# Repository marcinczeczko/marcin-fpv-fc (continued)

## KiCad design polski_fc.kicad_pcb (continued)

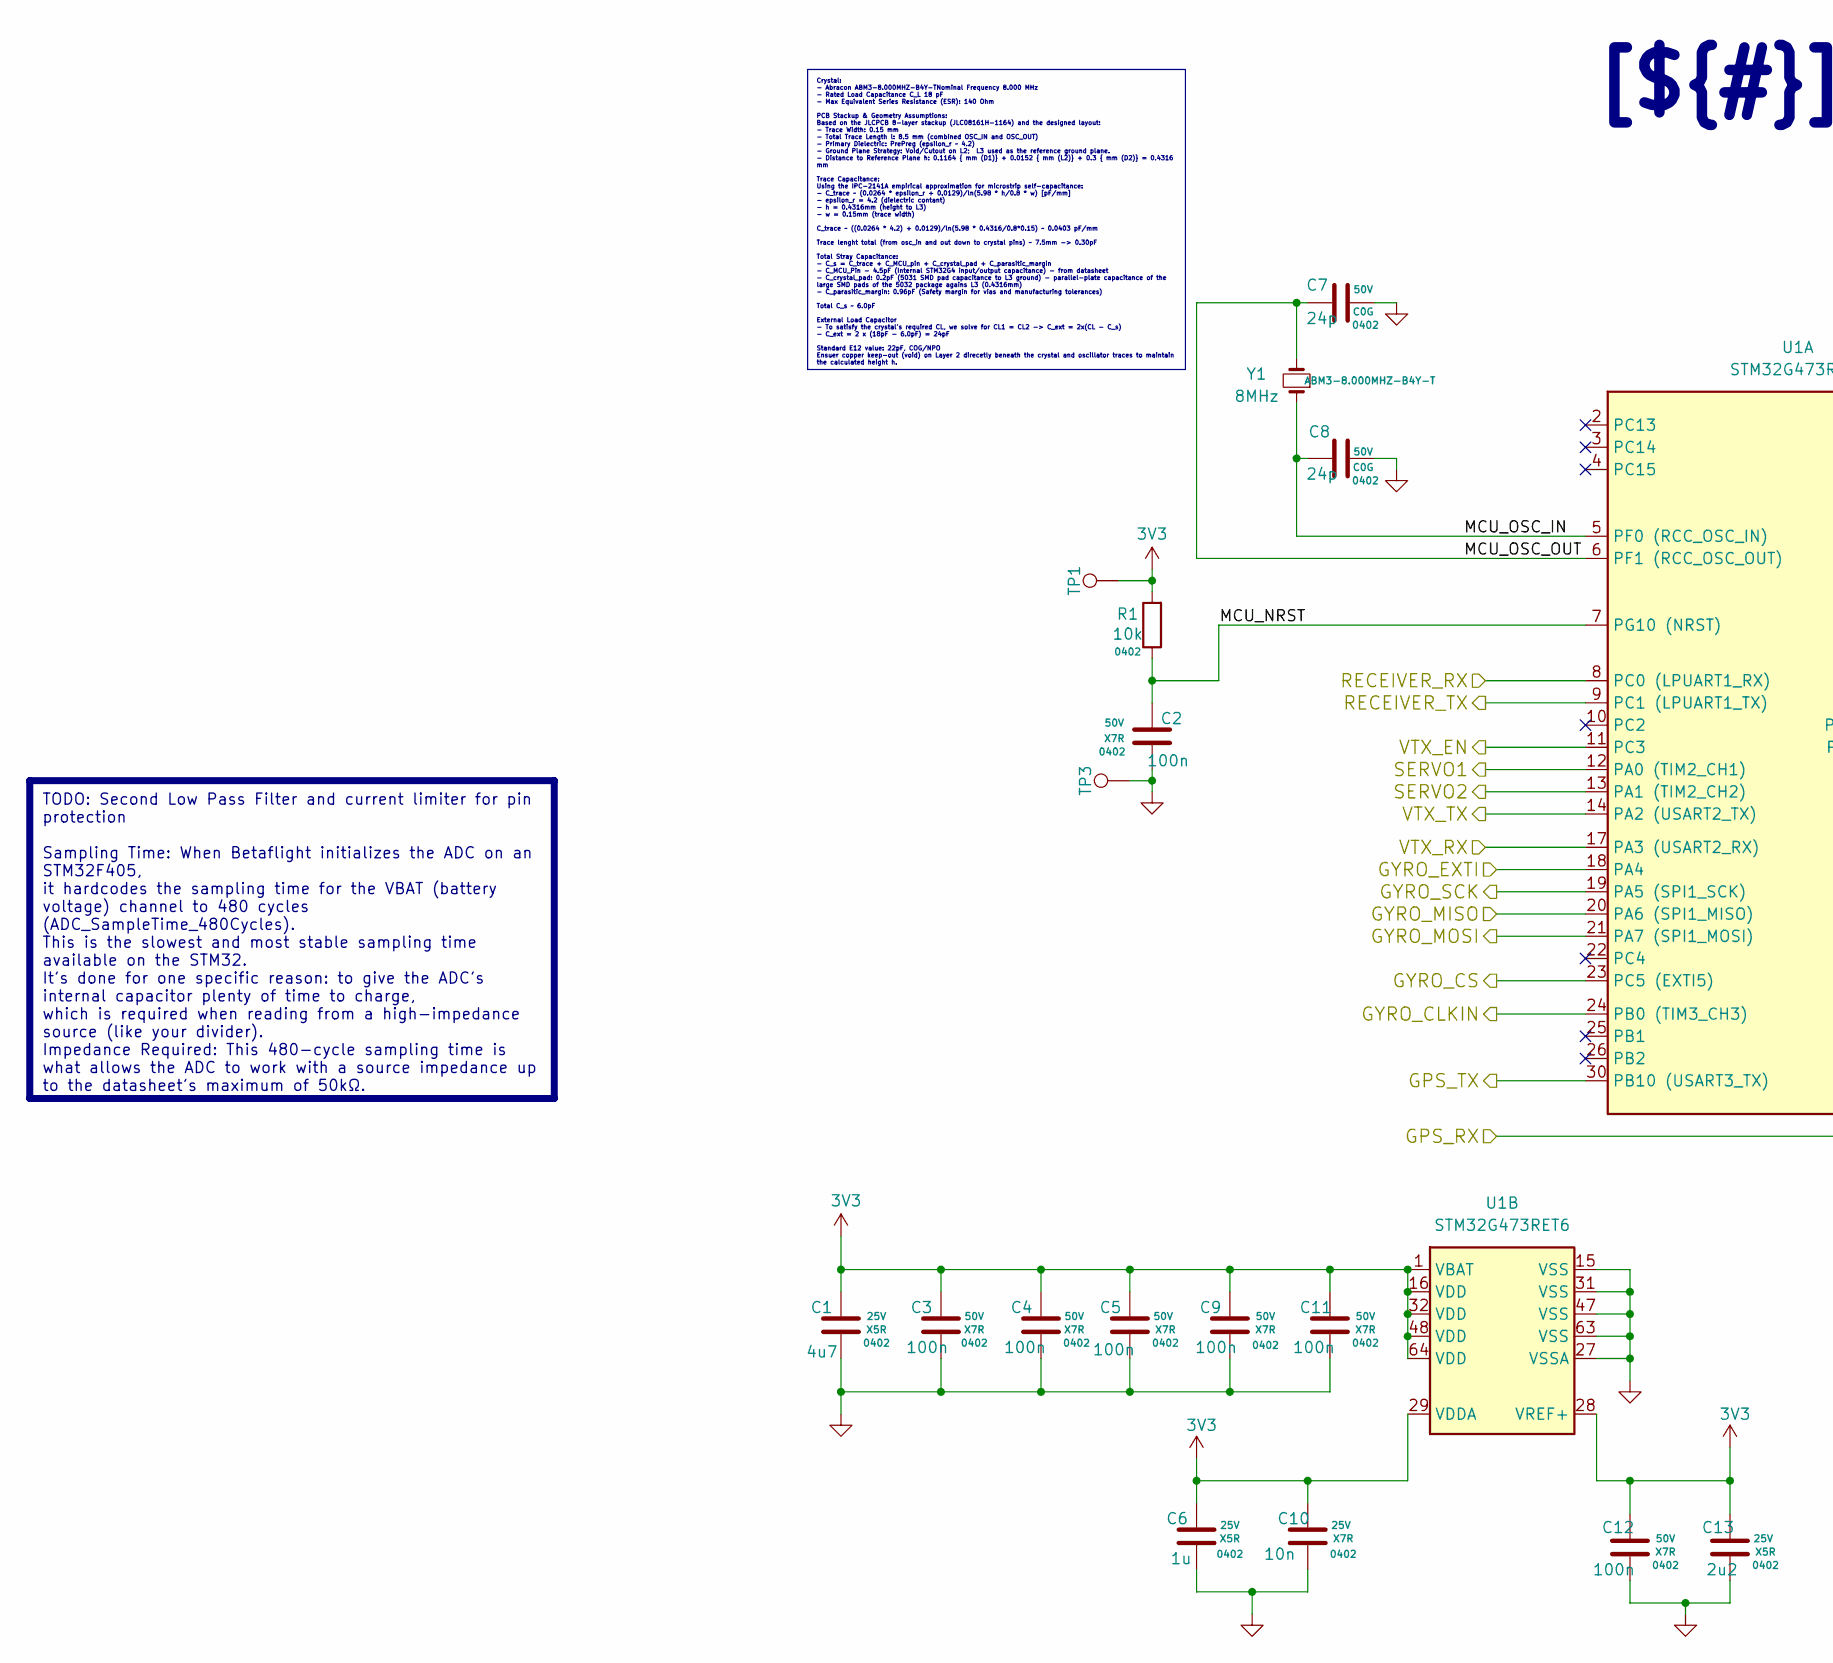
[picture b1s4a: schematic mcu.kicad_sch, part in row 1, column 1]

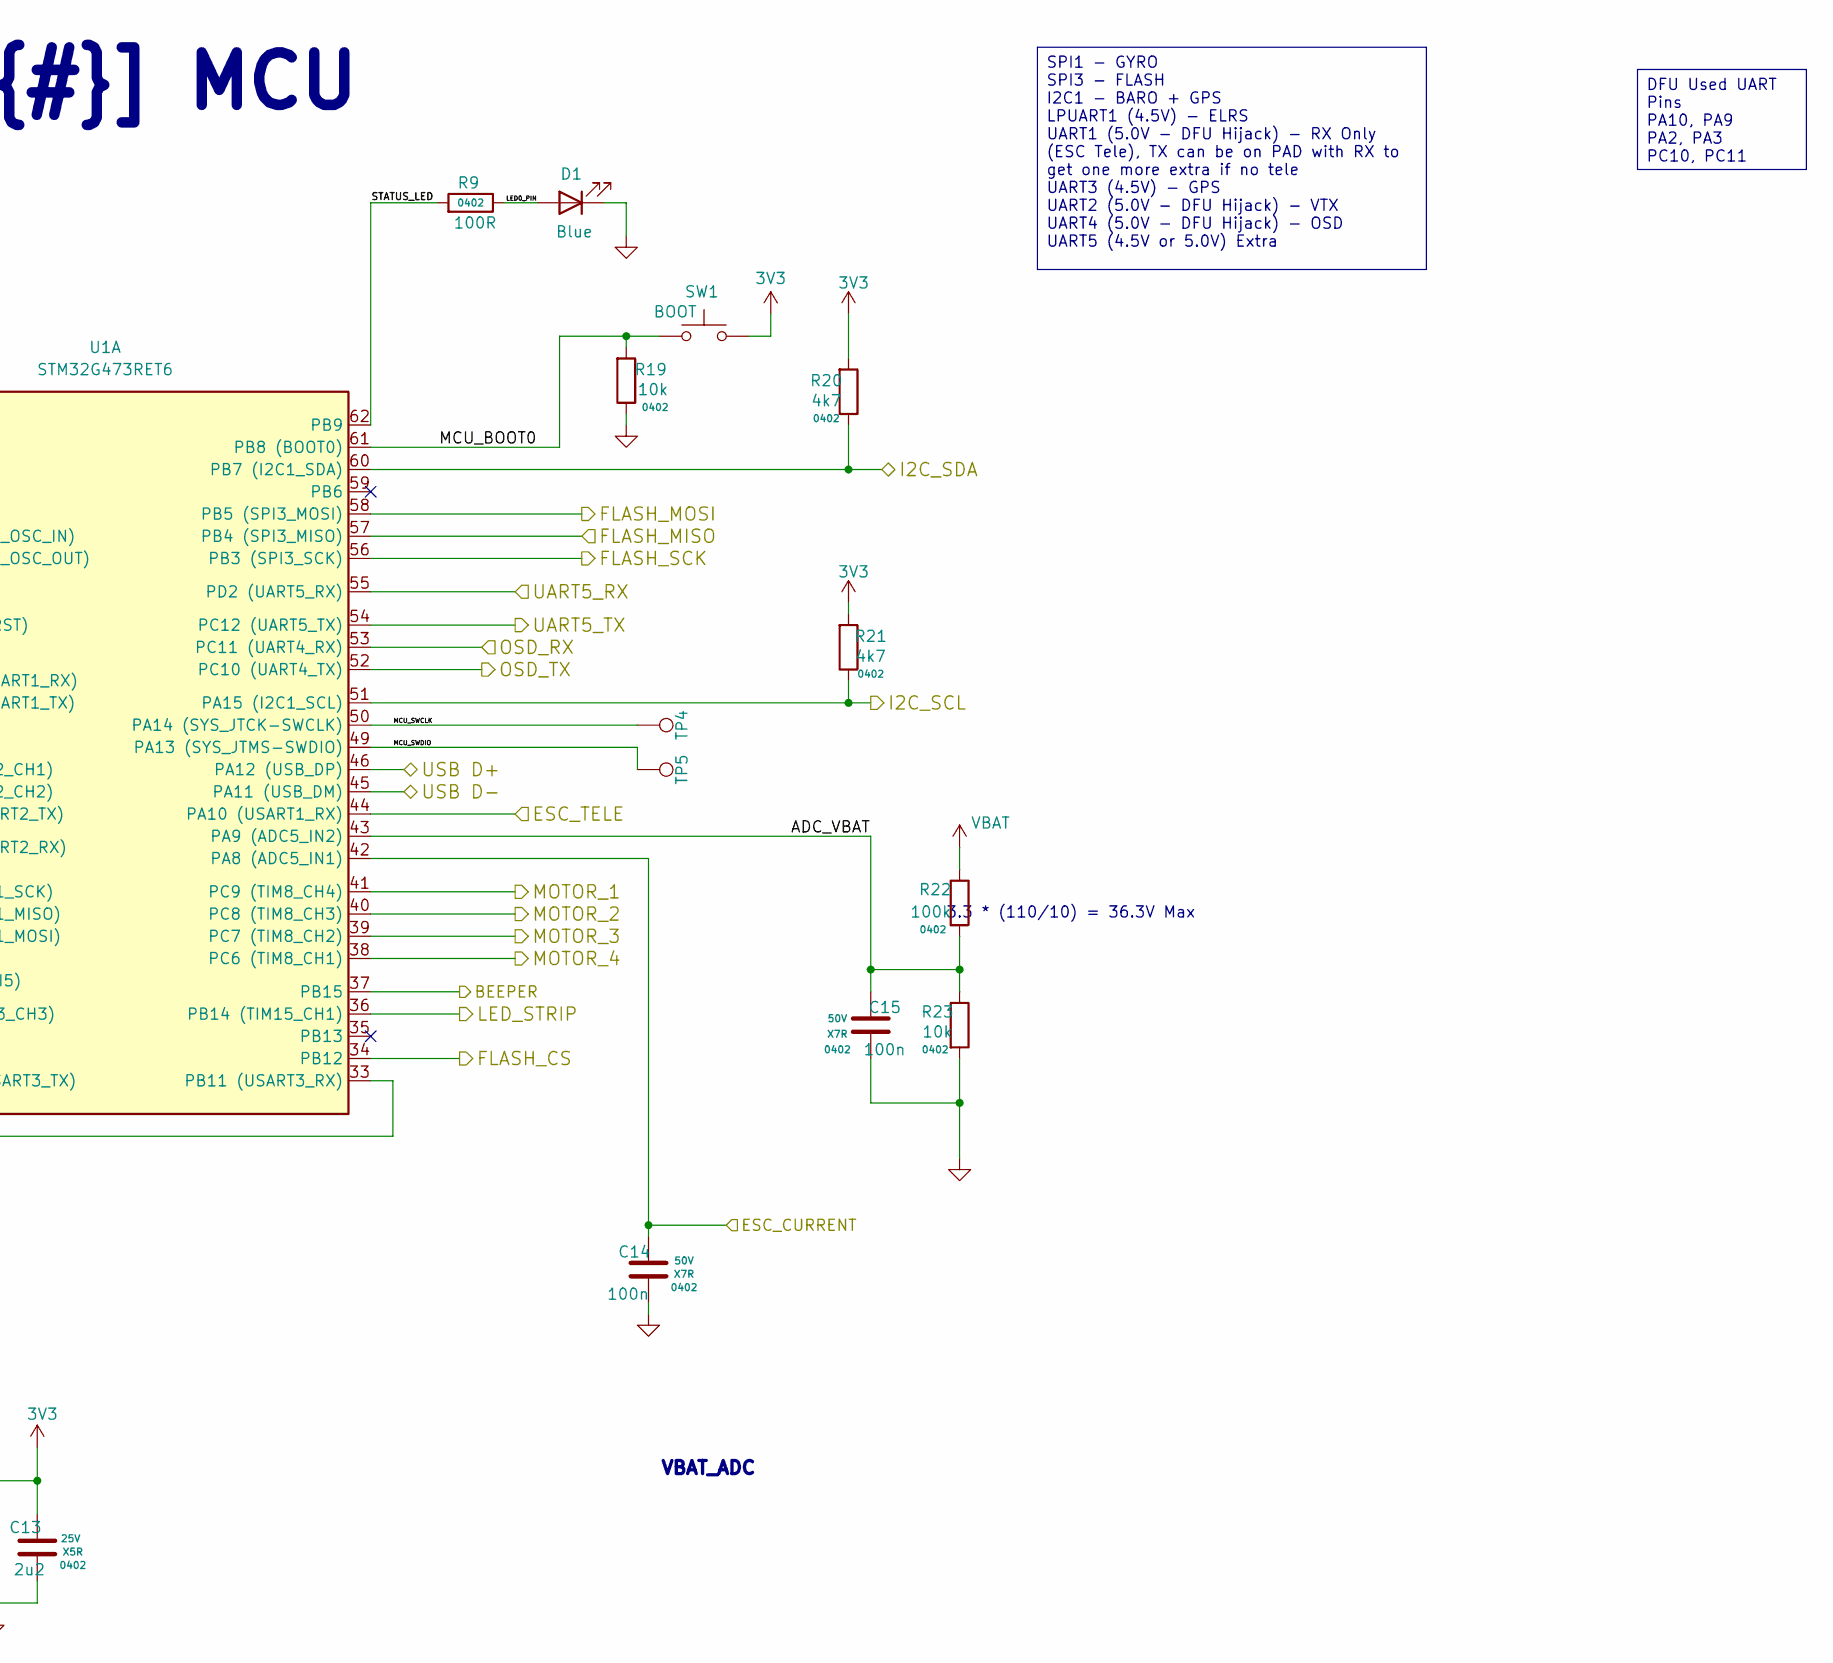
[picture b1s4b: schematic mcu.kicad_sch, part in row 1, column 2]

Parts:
C1: 4u7; C_0402; Voltage 25V; MANUFACTURER # GRM155R61C475KE15D; LCSC C426094
C2, C3, C4, C5, C9, C11, C12, C14, C15: 100n; C_0402; Voltage 50V; MANUFACTURER # GRM155R71H104KE14D; LCSC C77020
C6: 1u; C_0402; Voltage 25V; MANUFACTURER # GRM155R61E105KA12D; LCSC C77009
C7, C8: 24p; C_0402; Voltage 50V; MANUFACTURER # GCM1555C1H240FA16D; LCSC C1864480
C10: 10n; C_0402; Voltage 25V; MANUFACTURER # GRM155R71E103KA01D; LCSC C77013
C13: 2u2; C_0402; Voltage 25V; MANUFACTURER # GRM155R61E225KE11D; LCSC C385032
D1: Blue; LED_0402; MANUFACTURER # LTST-C281TBKT-5A; LCSC C364550
R1, R19, R23: 10k; R_0402; MANUFACTURER # RC0402FR-0710KL; LCSC C60490
R9: 100R; R_0402; MANUFACTURER # RC0402FR-07100RL; LCSC C106232
R20, R21: 4k7; R_0402; MANUFACTURER # RC0402JR-074K7L; LCSC C105870
R22: 100k; R_0402; MANUFACTURER # RP0402BRD07100KL; LCSC C7294193
SW1: BOOT; B3U-1000P; MANUFACTURER # B3U-1000P; LCSC C231329
TP1, TP3, TP4, TP5: 0.5mm; TestPoint-1mm
U1: STM32G473RET6; STM32G473RETx-LQFP-64_10x10mm_P0.5mm; MANUFACTURER # STM32G473RET6; LCSC C730120
Y1: 8MHz; ABM3; MANUFACTURER # ABM3-8.000MHZ-B4Y-T; Mouser # 815-ABM38000B4YT

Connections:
3V3: C1.1, C3.1, C4.1, C5.1, C6.1, C9.1, C10.1, C11.1, C12.1, C13.1, R1.1, R20.1, R21.1, SW1.1, TP1.1, U1.1 (VBAT), U1.16 (VDD), U1.28 (VREF+), U1.29 (VDDA), U1.32 (VDD), U1.48 (VDD), U1.64 (VDD); also elsewhere on the board
/Project Architecture/Blackbox/FLASH_CS: U1.34 (PB12); also elsewhere on the board
/Project Architecture/Blackbox/FLASH_DI: U1.58 (PB5 (SPI3_MOSI)); also elsewhere on the board
/Project Architecture/Blackbox/FLASH_DO: U1.57 (PB4 (SPI3_MISO)); also elsewhere on the board
/Project Architecture/Blackbox/FLASH_SCK: U1.56 (PB3 (SPI3_SCK)); also elsewhere on the board
/Project Architecture/IMU & Baro/BARO_I2C_SCL: R21.2, U1.51 (PA15 (I2C1_SCL)); also elsewhere on the board
/Project Architecture/IMU & Baro/BARO_I2C_SDA: R20.2, U1.60 (PB7 (I2C1_SDA)); also elsewhere on the board
/Project Architecture/IMU & Baro/GYRO_CLKIN: U1.24 (PB0 (TIM3_CH3)); also elsewhere on the board
/Project Architecture/IMU & Baro/GYRO_CS: U1.23 (PC5 (EXTI5)); also elsewhere on the board
/Project Architecture/IMU & Baro/GYRO_EXTI: U1.18 (PA4); also elsewhere on the board
/Project Architecture/IMU & Baro/GYRO_SCLK: U1.19 (PA5 (SPI1_SCK)); also elsewhere on the board
/Project Architecture/IMU & Baro/GYRO_SDI: U1.21 (PA7 (SPI1_MOSI)); also elsewhere on the board
/Project Architecture/IMU & Baro/GYRO_SDO: U1.20 (PA6 (SPI1_MISO)); also elsewhere on the board
/Project Architecture/Interfaces/BEEPER: U1.37 (PB15); also elsewhere on the board
/Project Architecture/Interfaces/ESC_CURR: C14.1, U1.42 (PA8 (ADC5_IN1)); also elsewhere on the board
/Project Architecture/Interfaces/LED_STRIP: U1.36 (PB14 (TIM15_CH1)); also elsewhere on the board
/Project Architecture/Interfaces/MOTOR1: U1.41 (PC9 (TIM8_CH4)); also elsewhere on the board
/Project Architecture/Interfaces/MOTOR2: U1.40 (PC8 (TIM8_CH3)); also elsewhere on the board
/Project Architecture/Interfaces/MOTOR3: U1.39 (PC7 (TIM8_CH2)); also elsewhere on the board
/Project Architecture/Interfaces/MOTOR4: U1.38 (PC6 (TIM8_CH1)); also elsewhere on the board
/Project Architecture/Interfaces/SERVO1: U1.12 (PA0 (TIM2_CH1)); also elsewhere on the board
/Project Architecture/Interfaces/SERVO2: U1.13 (PA1 (TIM2_CH2)); also elsewhere on the board
/Project Architecture/Interfaces/UART1_RX (RECV): U1.8 (PC0 (LPUART1_RX)); also elsewhere on the board
/Project Architecture/Interfaces/UART1_TX (RECV): U1.9 (PC1 (LPUART1_TX)); also elsewhere on the board
/Project Architecture/Interfaces/UART2_RX (TELE): U1.44 (PA10 (USART1_RX)); also elsewhere on the board
/Project Architecture/Interfaces/UART3_RX (GPS): U1.33 (PB11 (USART3_RX)); also elsewhere on the board
/Project Architecture/Interfaces/UART3_TX (GPS): U1.30 (PB10 (USART3_TX)); also elsewhere on the board
/Project Architecture/Interfaces/UART5_RX: U1.55 (PD2 (UART5_RX)); also elsewhere on the board
/Project Architecture/Interfaces/UART5_TX: U1.54 (PC12 (UART5_TX)); also elsewhere on the board
/Project Architecture/Interfaces/USB D+: U1.46 (PA12 (USB_DP)); also elsewhere on the board
/Project Architecture/Interfaces/USB D-: U1.45 (PA11 (USB_DM)); also elsewhere on the board
/Project Architecture/Interfaces/VTX_RX: U1.17 (PA3 (USART2_RX)); also elsewhere on the board
/Project Architecture/Interfaces/VTX_TX: U1.14 (PA2 (USART2_TX)); also elsewhere on the board
/Project Architecture/MCU/ADC_VBAT: C15.1, R22.1, R23.2, U1.43 (PA9 (ADC5_IN2))
/Project Architecture/MCU/LED0_PIN: D1.2 (A), R9.2
/Project Architecture/MCU/MCU_BOOT0: R19.1, SW1.2, U1.61 (PB8 (BOOT0))
/Project Architecture/MCU/MCU_NRST: C2.1, R1.2, U1.7 (PG10 (NRST))
/Project Architecture/MCU/MCU_OSC_IN: C8.1, U1.5 (PF0 (RCC_OSC_IN)), Y1.1
/Project Architecture/MCU/MCU_OSC_OUT: C7.1, U1.6 (PF1 (RCC_OSC_OUT)), Y1.2
/Project Architecture/MCU/MCU_SWCLK: TP4.1, U1.50 (PA14 (SYS_JTCK-SWCLK))
/Project Architecture/MCU/MCU_SWDIO: TP5.1, U1.49 (PA13 (SYS_JTMS-SWDIO))
/Project Architecture/MCU/OSD_RX: U1.53 (PC11 (UART4_RX)); also elsewhere on the board
/Project Architecture/MCU/OSD_TX: U1.52 (PC10 (UART4_TX)); also elsewhere on the board
/Project Architecture/MCU/STATUS_LED: R9.1, U1.62 (PB9)
/Project Architecture/MCU/VTX_EN: U1.11 (PC3); also elsewhere on the board
GND: C1.2, C2.2, C3.2, C4.2, C5.2, C6.2, C7.2, C8.2, C9.2, C10.2, C11.2, C12.2, C13.2, C14.2, C15.2, D1.1 (K), R19.2, R23.1, TP3.1, U1.15 (VSS), U1.27 (VSSA), U1.31 (VSS), U1.47 (VSS), U1.63 (VSS); also elsewhere on the board
VBAT: R22.2; also elsewhere on the board

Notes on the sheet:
3.3 * (110/10) = 36.3V Max
Crystal: - Abracon ABM3-8.000MHZ-B4Y-TNominal Frequency 8.000 MHz - Rated Load Capacitance C_L 18 pF - Max Equivalent Series Resistance (ESR): 140 Ohm PCB Stackup & Geometry Assumptions: Based on the JLCPCB 8-layer stackup (JLC08161H-1164) and the designed layout: - Trace Width: 0.15 mm - Total Tra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
TODO: Second Low Pass Filter and current limiter for pin protection Sampling Time: When Betaflight initializes the ADC on an STM32F405, it hardcodes the sampling time for the VBAT (battery voltage) channel to 480 cycles (ADC_SampleTime_480Cycles). This is the slowest and most stable sampling time a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
SPI1 - GYRO SPI3 - FLASH I2C1 - BARO + GPS LPUART1 (4.5V) - ELRS UART1 (5.0V - DFU Hijack) - RX Only (ESC Tele), TX can be on PAD with RX to get one more extra if no tele UART3 (4.5V) - GPS UART2 (5.0V - DFU Hijack) - VTX UART4 (5.0V - DFU Hijack) - OSD UART5 (4.5V or 5.0V) Extra
DFU Used UART Pins PA10, PA9 PA2, PA3 PC10, PC11
[${#}] ${TITLE}
VBAT_ADC

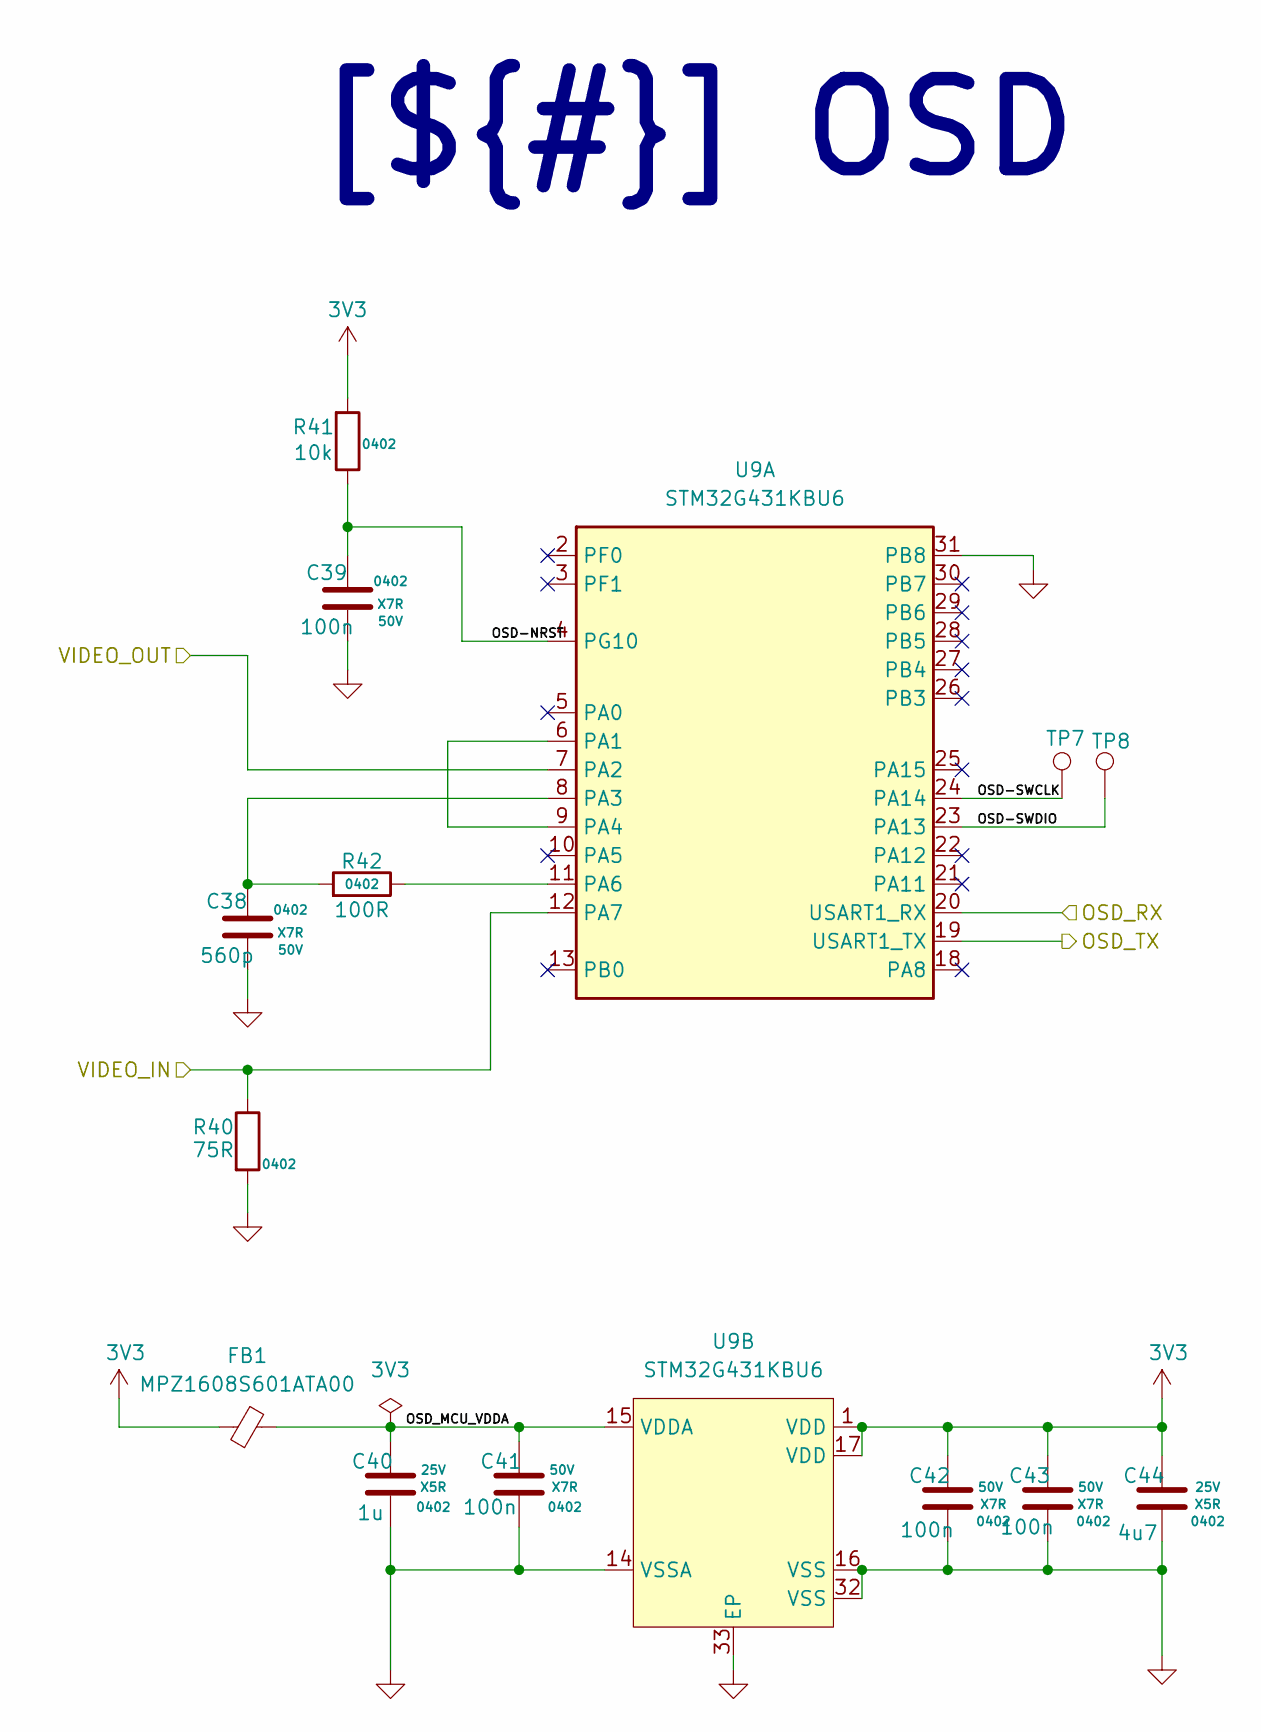
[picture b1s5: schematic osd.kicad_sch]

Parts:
C38: 560p; C_0402; Voltage 50V; MANUFACTURER # GCM155R71H561KA37D; LCSC C2941942
C39, C41, C42, C43: 100n; C_0402; Voltage 50V; MANUFACTURER # GRM155R71H104KE14D; LCSC C77020
C40: 1u; C_0402; Voltage 25V; MANUFACTURER # GRM155R61E105KA12D; LCSC C77009
C44: 4u7; C_0402; Voltage 25V; MANUFACTURER # GRM155R61C475KE15D; LCSC C426094
FB1: MPZ1608S601ATA00; Ferrite_0603_1608Metric; MANUFACTURER # MPZ1608S601ATA00; LCSC C107335
R40: 75R; R_0402; MANUFACTURER # RC0402JR-0775RL; LCSC C137841
R41: 10k; R_0402; MANUFACTURER # RC0402FR-0710KL; LCSC C60490
R42: 100R; R_0402; MANUFACTURER # RC0402FR-07100RL; LCSC C106232
TP7: OSD-SWCLK; TestPoint-1mm
TP8: OSD-SWDIO; TestPoint-1mm
U9: STM32G431KBU6; QFN-32-1EP_5x5mm_P0.5mm_EP3.45x3.45mm; MANUFACTURER # STM32G431KBU6; LCSC C529358

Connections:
3V3: C42.1, C43.1, C44.1, FB1.1, R41.1, U9.1 (VDD), U9.17 (VDD); also elsewhere on the board
/Project Architecture/Interfaces/VIDEO_IN: R40.2, U9.12 (PA7); also elsewhere on the board
/Project Architecture/Interfaces/VIDEO_OUT: U9.7 (PA2); also elsewhere on the board
/Project Architecture/MCU/OSD_RX: U9.19 (USART1_TX); also elsewhere on the board
/Project Architecture/MCU/OSD_TX: U9.20 (USART1_RX); also elsewhere on the board
/Project Architecture/OSD/OSD-NRST: C39.1, R41.2, U9.4 (PG10)
/Project Architecture/OSD/OSD-SWCLK: TP7.1, U9.24 (PA14)
/Project Architecture/OSD/OSD-SWDIO: TP8.1, U9.23 (PA13)
/Project Architecture/OSD/OSD_MCU_VDDA: C40.1, C41.1, FB1.2, U9.15 (VDDA)
GND: C38.2, C39.2, C40.2, C41.2, C42.2, C43.2, C44.2, R40.1, U9.14 (VSSA), U9.16 (VSS), U9.31 (PB8), U9.32 (VSS), U9.33 (EP); also elsewhere on the board
unnamed: U9.6 (PA1), U9.9 (PA4)
unnamed: C38.1, R42.1, U9.8 (PA3)
unnamed: R42.2, U9.11 (PA6)

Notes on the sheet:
[${#}] ${TITLE}

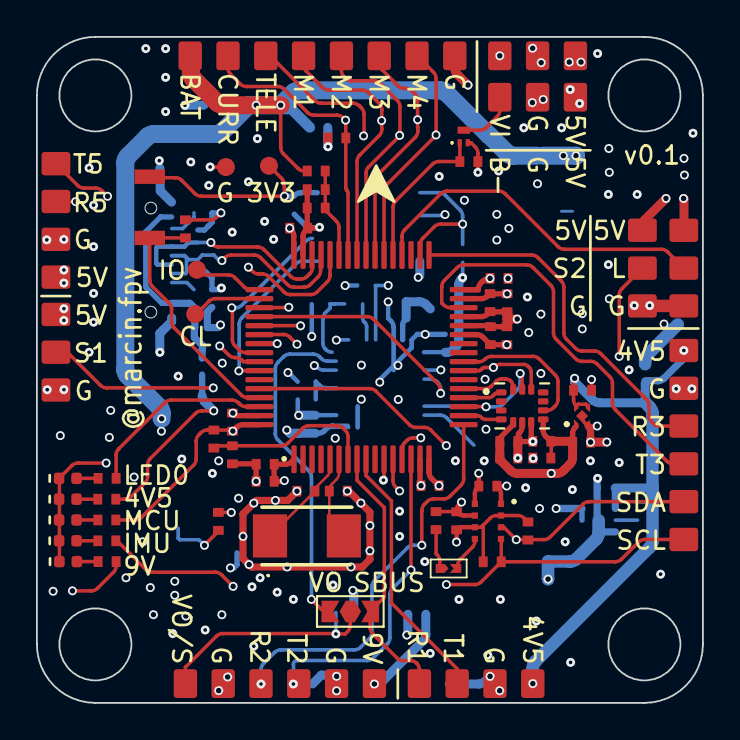
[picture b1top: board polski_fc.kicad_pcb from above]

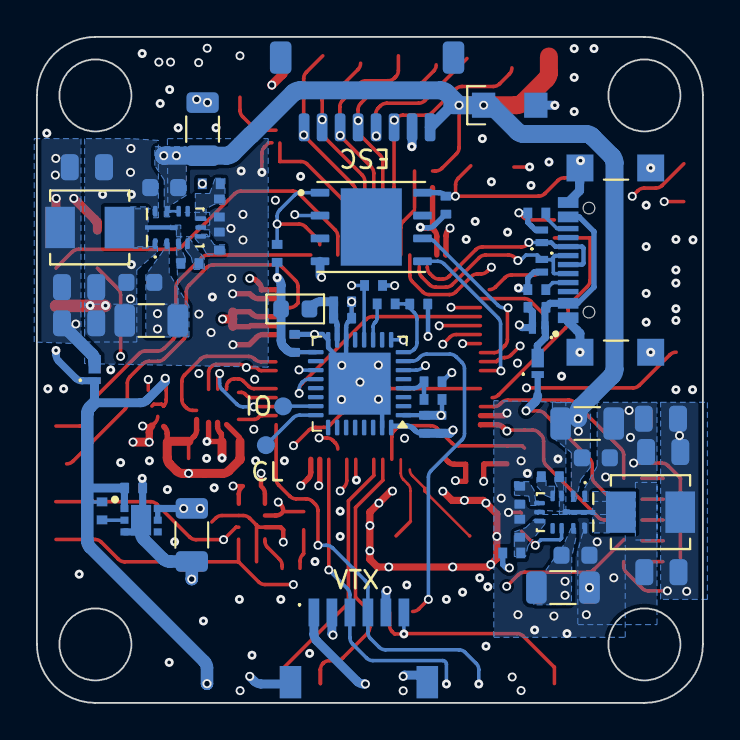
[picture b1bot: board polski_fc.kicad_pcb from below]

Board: 8 copper layers, 37.0 x 37.0 mm, 157 parts (59 on the bottom side), 80 nets.

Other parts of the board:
C32, C34, C35: 100n; C_0402
C33: 10n; C_0402
C36: 2u2; C_0402
JP1: Addr; SolderJumper-2_Open_TrianglePad1.0x1.5mm
R37: 10k; R_0402
R38: 100k; R_0402
U6: ICM-42688-P; PQFN50P300X250X97-14N
U7: DPS368XTSA1; XDCR_DPS368XTSA1

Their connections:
3V3: C32.1, C34.1, U7.2 (CSB), U7.6 (VDDIO), U7.8 (VDD); also elsewhere on the board
3V3-IMU: C33.1, C35.1, C36.1, R37.1, U6.5 (VDDIO), U6.8 (VDD); also elsewhere on the board
/Project Architecture/IMU & Baro/ADDR_JUMPER: JP1.2 (B), U7.5 (SDO)
/Project Architecture/IMU & Baro/BARO_I2C_SCL: U7.4 (SCK); also elsewhere on the board
/Project Architecture/IMU & Baro/BARO_I2C_SDA: U7.3 (SDI); also elsewhere on the board
/Project Architecture/IMU & Baro/GYRO_CLKIN: U6.9 (INT2); also elsewhere on the board
/Project Architecture/IMU & Baro/GYRO_CS: R37.2, U6.12 (AP_CS); also elsewhere on the board
/Project Architecture/IMU & Baro/GYRO_EXTI: U6.4 (INT1); also elsewhere on the board
/Project Architecture/IMU & Baro/GYRO_SCLK: U6.13 (AP_SCL); also elsewhere on the board
/Project Architecture/IMU & Baro/GYRO_SDI: U6.14 (AP_SDA); also elsewhere on the board
/Project Architecture/IMU & Baro/GYRO_SDO: U6.1 (AP_SDO); also elsewhere on the board
GND: C32.2, C33.2, C34.2, C35.2, C36.2, R38.2, U6.6 (GND), U6.7 (RESV_7), U7.1 (GND), U7.7 (GND); also elsewhere on the board
unnamed: JP1.1 (A), R38.1

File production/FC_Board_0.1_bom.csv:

Designator,Footprint,Quantity,Value,LCSC Part #
"C1, C44, C51",C_0402,3,4u7,
"C10, C33",C_0402,2,10n,
"C11, C12, C14, C15, C2, C26, C27, C3, C32, C34, C35, C37, C39, C4, C41, C42, C43, C5, C9",C_0402,19,100n,
"C13, C36",C_0402,2,2u2,
"C16, C17, C18, C20",C_1206,4,4u7,
"C19, C21, C23, C24",C_0603,4,100n,
"C22, C25, C40, C47, C48, C50, C6",C_0402,7,1u,
"C28, C29, C31, C45",C_0805,4,22u,
"C30, C46",C_0805,2,100n,
C38,C_0402,1,560p,
C49,C_1206,1,10u,
"C7, C8",C_0402,2,18p,
D1,LED_0402,1,Blue,
"D10, D11, D4",PESD5V0S1BL315,3,"PESD5V0X1BL,315",
D2,SMF_DO-219AB,1,SMF28A,
"D3, D5",SDM2A40CSP7B,2,SDM2A40CSP,
"D6, D7, D8, D9",LED_0402,4,Green,
FB1,Ferrite_0603_1608Metric,1,MPZ1608S601ATA00,
J2,JST_SH_SM08B-SRSS-TB_1x08-1MP_P1.00mm_Horizontal,1,JST-SH 1x08,
J3,JST-SH_SM06BSRSSTBLFSN,1,Digital_VTX_Connector,
J4,SAMESKY_UJ20-C-H-G-SMT-5-P16-TR,1,UJ20-C-H-G-SMT-5-P16-TR,
JP2,SolderJumper-3_Open_TrianglePad1.0x1.5mm,1,~,
"L1, L2",IND_SPM4020T-3R3M-LR,2,3u3,
Q1,NX138AKMYL,1,NX138AKMYL,
"R1, R19, R23, R25, R37, R39, R41",R_0402,7,10k,
"R20, R21",R_0402,2,4k7,
"R22, R28, R32, R35, R38, R8",R_0402,6,100k,
R24,R_0402,1,24k9,
"R26, R27",R_0402,2,5.1k,
R29,R_0402,1,12k4,
"R30, R33, R34",R_0402,3,470R,
R31,R_0402,1,2k2,
R40,R_0402,1,75R,
"R42, R9",R_0402,2,100R,
SW1,B3U-1000P,1,BOOT,
TP7,TestPoint-1mm,1,OSD-SWCLK,
TP8,TestPoint-1mm,1,OSD-SWDIO,
U1,STM32G473RETx-LQFP-64_10x10mm_P0.5mm,1,STM32G473RET6,
"U2, U3",LMR33630CRNXR,2,LMR33630CRNXR,
U4,NCP187x-WDFNW6_2x2_0.65P,1,NCP187AMT330TAG,
U5,TCR3RMx-DFN4F_TOS,1,TCR3RM33A,
U6,PQFN50P300X250X97-14N,1,ICM-42688-P,
U7,XDCR_DPS368XTSA1,1,DPS368XTSA1,
U8,SON127P500X600X80-9N,1,W25Q128JVPIQ,
U9,QFN-32-1EP_5x5mm_P0.5mm_EP3.45x3.45mm,1,STM32G431KBU6,
Y1,Crystal_SMD_3225-4Pin_3.2x2.5mm,1,8MHz,

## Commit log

2026-02-09 FC 0.1 layout
2026-02-09 Added silkscren
2026-02-09 Add return vias for SPI and fixed some rouding traces
2026-02-10 Crystal change, gnd cut-out for crystal, bom update
2026-05-05 feat: implement hierarchical KiBot automation and advanced GitHub Actions CI/CD
2026-05-05 chore: update .gitignore to exclude KiCad local settings
2026-05-05 chore: optimize .gitignore and purge git index of redundant files
2026-05-05 fix: resolve unknown variant error in KiBot GitHub Action by renaming variable to target
